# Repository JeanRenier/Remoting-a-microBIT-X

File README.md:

**Introduction.**
 I became a licensed radio amateur when I retired some 10 years ago, my call is ON4JRT.
 Alas, moving to an apartment building a few years ago I lost the possibility to install a decent antenna. Even if I had the permission to install an antenna on the roof, the QRM generated by the building itself and the surrounding town would probably have made a clean reception almost impossible.
 A friend, who lives in the country side and to whom I am eternally grateful, came to my rescue and allowed me to install a remote transceiver and a modest antenna in his garden.

There are several remote transceiver projects described on the internet. Whilst they all are certainly more sophisticated and more performing than the rather simple system presented here, they are also much more demanding in resources (space, power, money, ...). I wanted a small stand alone system that would be self sustaining (save for an internet connection), not too conspicuous and not too expensive.
 Hence this project, which eventually was successful after a few trials. Its aim is to provide me with an remotely located transceiver for my own use, it is by no means a &quot;public&quot; transceiver available to other OM&#39;s.
 Like all engineering endeavor it consist of a series of choices and compromises, so don&#39;t shoot the pianist.

**The concept.**
 The remote transceiver system consists of several parts: A transceiver (obviously), a HF antenna, a battery, a small solar panel, a controller with a WiFi transceiver and a controller for the solar panel. Except for the HF antenna and the solar panel everything is enclosed in a small plastic housing of about 5 liter in volume.
 The remote transceiver communicates (i.e. the bidirectional data flows for sound, CAT and control) over the internet with a home device. This home device contains a simple user interface allowing some control over the remote device. Sound input and output is also available on this home device, as is a CAT interface. If I were a better PC/Posix software programmer I would probably gotten rid of the home device. Having the home device as a physical thing eases however the development (at least for me) while not adding too much to the cost.

**The transceiver.**
 After some search, I came across the µBIT-X (&quot;[https://www.hfsignals.com/index.php/ubitx/](https://www.hfsignals.com/index.php/ubitx/)&quot;) sold as a semi assembled kit developed by Ashhar Farhan (VU2ESE), now in its 6th version (I got the previous version for this project). It is a simple but rather well designed multi band HF QRP transceiver based on a double super architecture and bidirectional amplifiers (it uses almost all the building blocks for reception as well as for transmission). It is well documented, has a large fan club and most of the suggested improvements are officially endorsed.
 Coming out of the box, it needs to be calibrated and tuned (a bit). Apart from the CAT baud rate I didn&#39;t feel the need to modify anything. Obviously I didn&#39;t install the LCD or the rotary encoder (since nobody would look/touch at it), all control is performed via the CAT connection over the internet from the home device, and even then, very little of the CAT commands are really used.

**The µBIT-X controller, hardware.**

Beginning with the power supply: a DC/DC controller reduces the battery voltage to 4V, from there three linear regulators make the necessary 3.3V digital, 3.3V analog and 1.8V respectively.

An ESP32-WROOM module is the core of the controller, this awesome microprocessor includes the WiFi transceiver, performs all relevant IP chores and runs all the application software.
 It then interfaces a WM8731 codec by a I2Sbus for the digital sound and a I2Cbus for its control. This codec is a straight forward 16bit stereo ADC and DAC combination, it is programmed in this case for a sampling rate of 8kHz, yielding a sound bandwidth of 3400Hz, its dynamic range exceeds 90dB. The analog sound input and output from the codec goes through a set of isolating 600 Ohm 1:1 audio transformers and trimpots to the µBIT-X sound stages.
 The first UART of the ESP32 is exclusively used for programming and debugging.

The second UART interfaces the CAT of the µBIT-X including a PTT line. This interface is isolated with a set of optocouplers, limiting the baud rate to 4800. Note that the RD and TD lines of this interface actually bypass the USB-UART chip on the Arduino Nano board of the µBIT-X, luckily a series resistor was placed in the RD line of this Arduino Nano, hence no track cutting was nescessary.
 The third UART interfaces the Solar Controller board, it is also fit with optocouplers.
 At last the board is equipped with a PMOS switch capable of more than 2A to power the µBIT-X itself when required.

An additional small board comprising a simple tandem match type VSWR bridge is mounted directly on the antenna input/output of the µBIT-X. The detected forward and reflected signals are fed into the ADC inputs of the ESP32. With the help of some math and calibration, it gives a rather good indication of the HF power and VSWR during transmit.

**The µBIT-X controller, software.**

The software was build on the Arduino IDE (version 1.8.12) with the ESP32 plug in and libraries (version 1.0.4). It took several months of writing and careful testing, having the home device nearby was a great help.
 The software was not especially designed to be universal or portable. The several parameters like the IP addresses, URL&#39;s, etc. are &quot;hard coded&quot; in the software, no attempt was made for now to store them in a file structure or other form of non volatile memory. Hence there is no way to change them without recompiling the entire software.
 The software includes the interesting possibility of being updated &quot;over the air&quot;, i.e. via the WiFi as per the method recommended by Espressif. This was tested but not yet used, an additional port forwarding on the remote router is needed tor this.

The setup part of the software starts with the initialization of the several internal and external peripherals. After that a WiFi connection with one of the friendly WiFi AP&#39;s is established, that done the µBIT-X Controller will synchronizes with an NTP server, checking in at a DDNS server and send a short e-mail as a sign of live. Once the setup is done two endless loops will take care of business until powered off.
 One of the loops is dedicated to the audio interface, seeing to it that the digital sound samples flow in and out the codec through the I2Sbus at a constant rate of 8kHz.
 The other loop will handle the incoming and outgoing UDP packets. Outgoing packets are sent only when incoming UDP packets are present, i.e. only during a connection between the µBIT-X controller and the home device.

The data in each packet is split into three separate flows, the biggest one being the sound, a smaller one for the CAT going directly to/from the µBIT-X and the last one for the housekeeping of the µBIT-X Controller itself and the Solar Controller.

During a connection there is a UDP flow of 25 packets per second in each direction. Each packet has 660 bytes is build as follows:
 - bytes 0...639 : 320 16bit sound samples, 8000 samples/s

- byte 640...641 : packet count and control byte, including the PTT bit

- byte 642...646 : CAT bytes, max 5 to/from the µBIT-X

- byte 647...659 : CTL bytes, max 13 to/from the Solar Controller
 The sound samples of the incoming packets are stored in a circular buffer of 1s. Currently there is no provision made to cope with lost packets, if the circular buffer runs out, silence is send to the codec until its filled again for at least a quarter. Packet loss has not been a problem so far, typically no more than one packet per thousand gets lost.
 Likewise, differential drift of the sample clock, the 8kHz sampling rates at send and receive sides are not exactly equal, is simply ignored, though I may change this in future.

A few words about the IP addressing. In normal circumstances both the home device and µBIT-X Controller are connected to their respective WiFI AP&#39;s that are typically part of a modem router devices provided by Internet Access operators. The IP addresses of these devices are variable over time as the operators see fit. Hence the use of a DDNS server, the free service &quot;www.duckdns.org&quot; was chosen here. Both sides of the link are then known by their URL&#39;s i.e. &quot;remote\_name.duckdns.org&quot; and &quot;home\_name.duckdns.org&quot; respectively.
 That is one problem solved, still the packets need to pass the modem routers and be directed to the devices. This is done by setting a port forwarding for the appropriate port number in the modem router at both sides.
 Most modem routers have the tendency to assign a new IP address to the devices each time they connect. In order to avoid that, fixed IP addresses are organized for each device, hence the port forwarding can be set once and for all. The fixed IP addresses should carefully be chosen in order not to disturb the other IP stations on the local area (i.e. choosing one outside of the DHCP range of the modem).
 A more elegant solution to avoid the fixed IP addresses and the port forwarding settings in the modem routers would be the use of the UPnP method. There are good libraries for this method, e.g. &quot;[https://github.com/ofekp/TinyUPnP](https://github.com/ofekp/TinyUPnP)&quot;, with which I played a bit. It probably works but I was not able to test it due to some issues with my own modem router, so I stick with the port forwarding and fixed IP addresses for now.

**The solar panel controller.**
 The µBIT-X controller board (see further) takes about 38mA during normal operation (the µBIT-X itself being turned off), this was deemed too much to have it continuously running. Hence a scheme was preferred where the remote transceiver would become available through the internet for a few hours everyday at some predetermined time, e.g. from 8 o&#39;clock in the evening till midnight. This scheme works for me, though it may not be the case for everybody.

For this alarm clock/timer function a 24 hour real time clock was implemented in software. The power on time, the power off time and also the current time are settable remotely once a connection with the home device has been made.
 Besides of the above function the solar controller board is also supervising the charge of the battery. This function is kept extremely simple: when the battery voltage rises higher than 12.3V a PMOS switch is opened prohibiting the further charging of the battery from the solar panel. Likewise, if the battery voltage falls below 9.3V an other PMOS switch will cut the load (i.e. the rest of the system) in order to protect the battery from deep discharge damage. As the solar panel itself behaves very much like a current source and yields at most about 0.6A, no attempt is made to limit the charging current, it remains well below the maximum charging current of the Li-Ion battery.

This little board was designed some four years ago, it is built around the ATtiny84 chip and is furthermore connected via a serial port to the µBIT-X controller for housekeeping, such as the above mentioned timings, the battery voltage and the temperature inside the box. It takes a mere 3mA (continuously) from the battery.

**The battery.**
 Nothing very much is to be said about the battery, it is just an assembly of 18 Li-Ion cells of the 18650 format, 6 in parallel and 3 in series, yielding a nominal voltage of 11.1V and a capacity of 13Ah.
 Nothing is foreseen to perform load balancing, as is typical for Li-Ion batteries. After three &quot;campaigns&quot; in the field of 6 months each, no significant voltage drift was noted on the individual cell groups. This may be due to the rather gentle use of this battery, it is used mostly when nearly full (close to 12V), charged with no more than 0.6A (limited by the solar panel) and discharged with no more than 1.5A (µBIT-X transmitting) and the latter only during short periods.
 There is some concern about the temperature range of the the Li-Ion batteries: 0...40°C, which can easily be overreached during cold winters and hot summers. A thin Aluminum sheet is foreseen behind the south side of the housing to provide some shade for it.

**The housing.**
 A regular fridge/kitchen type PE box with a watertight lid of roughly 300\*200\*100mm (ca. 5 liter) was chosen as a housing for the entire remote system. An unorthodox choice, but there were never any problems with rain or weather during the accumulated 18 plus months of outdoor live so far.
 The box is traversed by two cables, one for the HF antenna (RG 58 coax) and one for the solar panel (round flexible twin electricity cable), both foreseen with pressure glands.
 Two &quot;feet&quot; are furthermore foreseen to enable the box to stand upright with its 200mm side vertical.
 The rear part of the box is reserved for the battery, the front part for the WiFi antenna (a double biquad), the in between space is filled with the µBIT-X, the µBIT-X controller and the solar controller. It was a bit of a shoe horn exercise, but nobody did complain...
 A few pouches of silica gel drying agent were inserted before the final closure of the lid.

**The solar panel.**
 The solar panel looks a bit like a picture frame, a slim Aluminum frame holds two sheets of glass between which 35 poly-crystalline photo voltaic cells are mounted in series. Its dimension is 330\*290mm. It is rated 10W by the manufacturer, if exposed perpendicular to the sun during a clear day it would yield about 17.5V (open circuit) and 0.6A (short circuit). It is installed in the garden more or less in an open space, near to the remote transceiver box, facing south and tilted at 45°.
 Theoretically, considering the statistics for my part of the world, it would yield 3.5Ah on an average summer day and 0.7Ah on an average winter day. Plenty to play with, at least during summer.

**The antenna.**
 Discretion is the keyword here, a simple 20m band wire dipole was installed horizontally between the trees in the garden. For practical reasons the resonant feed line design was chosen here, the height above the ground is about 3.5m. Alas, too low to make it a good DX antenna, but then it was that or nothing. The antenna is entirily made of RG58 cable, a nylon rope runs along with it for improved strength.
 The antenna impedance was measured and a small fixed LC circuit was installed in the remote transceiver box as an antenna tuner of sorts to ensure that the VSWR remains below 1.5.
 It was noted that the VSWR varies from 1.2 to 1.5 depending the weather.

**The home device, hardware.**
 The hardware of the little home device is very similar as that of the µBIT-X Controller. The sound is connected to the audio input/output of a PC with a 3.5mm audio jack. The incoming sound is also diverted to a small (30mm) loudspeaker to monitor the received signal.
 Note that the sound levels are kept intentionally high (i.e. around 1Veff), this in order to maximize the S/N ratio. The sound input/output towards the PC must hence be set accordingly (maximum for the output and almost nil for the input).
 The second UART is led through a UART-USB chip and is used for the CAT. The USB connection is also used for powering the home device. Further peripherals are a small OLED display (128\*64 pixels) connected to the I2Cbus (to monitor some vital parameters of the remote), a rotary encoder (to change the frequency), a potentiometer (speaker volume) and a toggle switch (to start/stop the connection with the remote).

**The home device, software.**
 The software of the little home device is also very similar to that of the µBIT-X Controller. No NTP synchronization or e-mail sending, instead the OLED display is configured during setup.
 During looping, the sending of packets is controlled by the toggle switch. Control and CAT messages coming from the remote are parsed and put on the OLED display: current frequency and mode, HF power out, VSWR, received packet count (at both ends), RSSI of the WiFi link (at both ends), battery voltage and temperature inside the housing.

A few words about the handling of the CAT messages. By design the µBIT-X emulates (at least the meaningful part of) the CAT messages of the Yeasu FT817/FT857 transceiver. This works well when the µBIT-X is connected directly to a PC, I could however not make it work when connected to through the chain of devices and the internet, most probably a question of delay.
 The following scheme was then implemented: The home device emulates in itself the above transceivers, responding immediately to satisfy the application on the PC. If something is changed (in practice the frequency or the mode) the corresponding message is send over the internet to the remote µBIT-X controller and to the µBIT-X itself. Any response of the latter is returned over the internet to the user interface of the home device.
 This scheme works well with Fldigi, however not at all with WSJT-X for reasons I have yet to understand. As for the PTT, three methods are simply used in parallel: the DTR method, the CAT method and the VOX method (implemented in software).

**Construction notes.**
The PCB&#39;s were designed with KiCad (version 5.1.6) in the form of a two layer board with generous ground planes. Most of the components are SMD though still solderable by hand.
 The board assembled in one panel were manufactured by jlcpcb.com, they offer an excellent and fast service. Care was taken to get all the boards within an area of 100\*100mm, their more or less permanent prototype discount offer.
 Most of the components were purchased at &quot;www.tme.eu&quot; and &quot;[www.r](http://www.reichelt.com/)[eichelt.com](http://www.reichelt.com/)&quot;. The more exotic components (OLED display, audio transformers, ESP32-WROOM module, WM8731A, …) were purchased at &quot;[www.aliexpress.com](http://www.aliexpress.com/)&quot;, the stuff is on the road for about 6 weeks, but the price is unbeatable.

In order to load the software into the ESP32 with the Arduino IDE, a small UART-USB module should be connected to the first UART (debug, only the RD, TD and GND lines), the boot strap should be shorted and the reset button should be pressed.
 The Solar Controlled was designed several years earlier, its software was made with AVR Studio 4. Alas, there is no Arduino IDE support for the ATtiny84.
 Finally, the housing of the home device was 3D-printed (a little box of 100\*50\*30mm), it was designed with OpenScad.

**Performance of the system as a whole.**

I am active only on the 20m band for now, the antenna being strictly monoband, and then mostly in the popular FT8 mode. With the 6...7W of output power it seems that I suffer some 10...15dB disadvantage versus other stations (difference of their S/N report versus my S/N report). This is probably more an issue of the QRP nature of the µBIT-X than the fact it is connected via the internet.
 The additional time delay due to digitization and buffering of the sound does not seem to have a significant effect, it is about 0.7s.

An other concern is the lack of cooling in the rather hermetic non metallic housing. When busy for one hour atempting QSO&#39;s in FT8, the temperature inside the housing will rise by typically 5°C. Not too bad, but then it says little about the temperature of the power FET&#39;s of the PA. Initial tests however indicated that their rather small radiators didn&#39;t became too hot even after several minutes of transmitting.

Battery drain of the remote part:
 - Solar Controller: 3mA (continuous)
 - µBIT-X Controller: 38mA (when awake)

- µBIT-X receiving: 175mA (when connected with the home device)
 - µBIT-X transmitting: 1125mA (when transmitting a single tone at 6W)

**Further improvements and other considerations.**
 Since the µBiT-X is multi band, as a further evolution of this project, I intend to have a multi band antenna (at least adding the 40m band) and some form of switchable/variable antenna tuner.

Some trick to capture the speed of rotation of the rotary encoder on the home device and to vary the frequency step accordingly would be useful. Now each step is strictly 100Hz, which is rather inconvenient. Making WSJT-X&#39;s CAT work with the home device would also be nice.
 Currently there is no provision made as for internet security, i.o.w. anybody with the right format of UDP packets can access the remote device and use it (he/she has still to know the relevant URL of course). Some scheme with an encrypted signature (e.g. HMAC style) inside each packet authenticating the home device would be an improvement.
 Though the current design is intended for the use with digimodes, it can easily be adapted for voice operations. Adding a microphone amplifier and a PTT switch input would then be required.

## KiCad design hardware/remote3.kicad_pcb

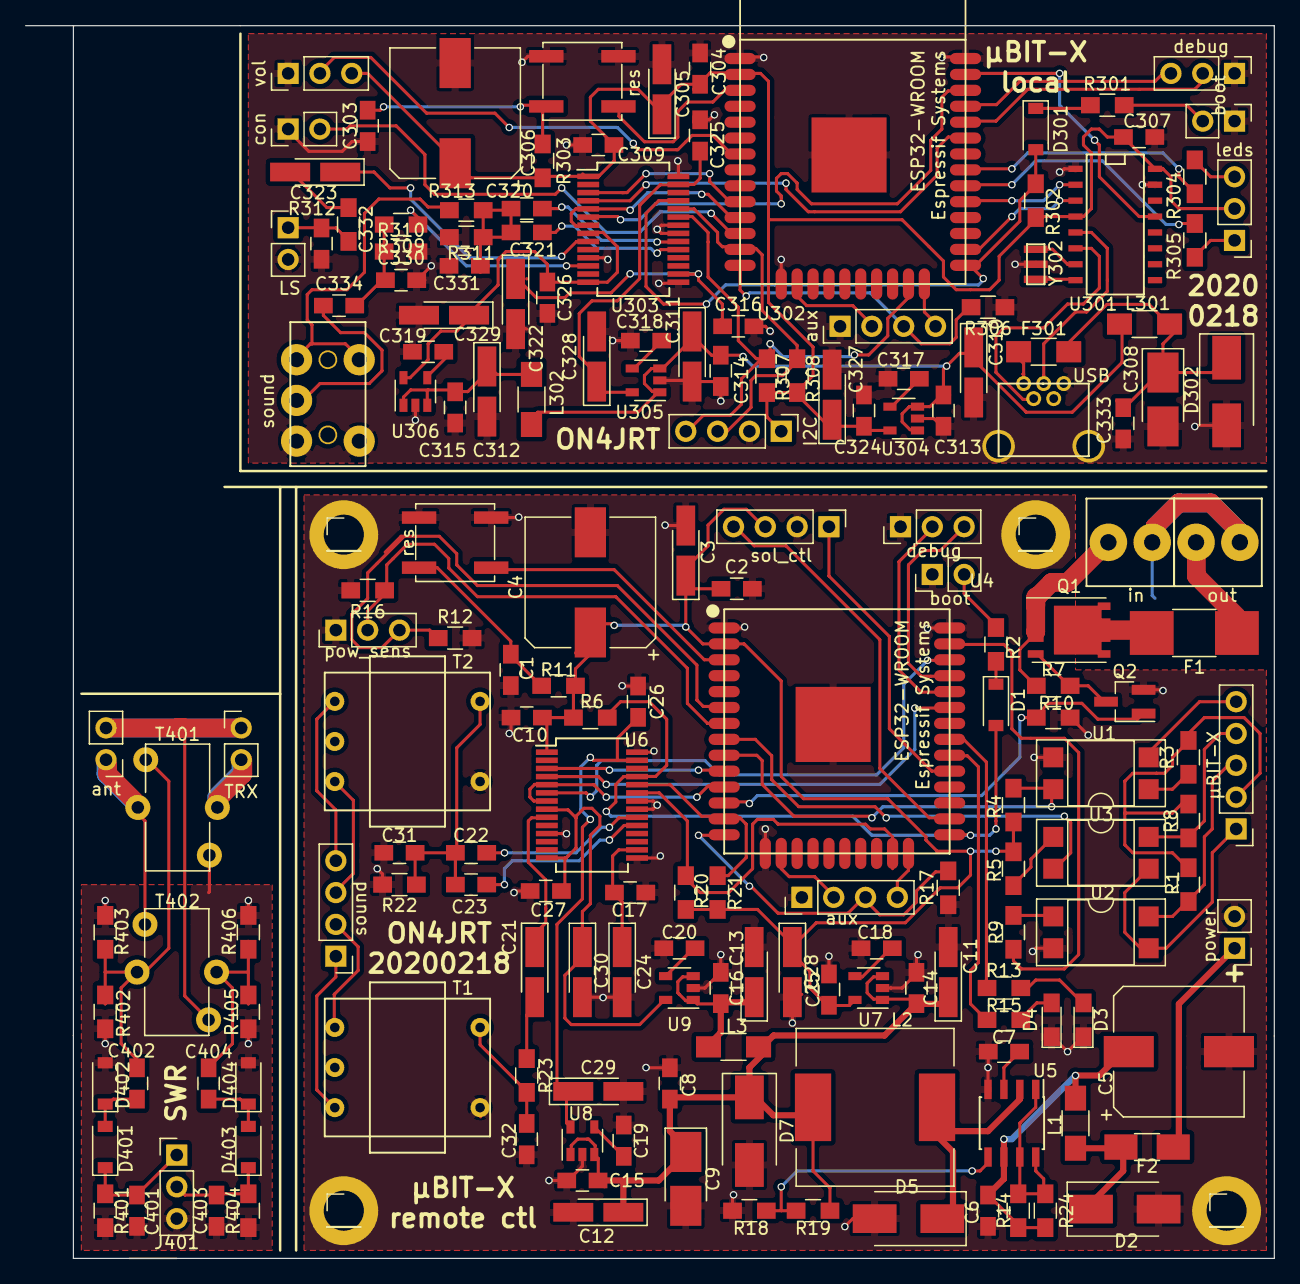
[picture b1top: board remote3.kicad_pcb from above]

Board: 2 copper layers, 99.7 x 98.4 mm, 182 parts (0 on the bottom side), 123 nets.

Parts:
 : hole; Pin_Header_Straight_1x01_Pitch2.54mm
 #2,  #3,  #4: hole; Pin_Header_Straight_1x01_Pitch2.54mm
C1, C303: 10n; C_0805_HandSoldering
C2, C6, C8, C10, C14, C15, C16, C17, C22, C23, C25, C26, C27, C304, C307, C309, C313, C314, C315, C316, C320, C321, C324, C325, C326, C333, C334, C401, C402, C403, C404: 100n; C_0805_HandSoldering
C3, C305: 1.5u; CP_Tantalum_Case-A_EIA-3216-18_Hand
C4, C306: 1500u; CP_Elec_10x10
C5: 470u; CP_Elec_10x10
C7, C18, C19, C20, C31, C32, C317, C318, C319, C330, C331, C332: 470p; C_0805_HandSoldering
C9, C308: 100u; CP_Tantalum_Case-B_EIA-3528-21_Hand
C11, C12, C13, C21, C24, C28, C29, C30, C310, C311, C312, C322, C327, C328, C329: 10u; CP_Tantalum_Case-A_EIA-3216-18_Hand
C323: 100u; CP_Tantalum_Case-A_EIA-3216-18_Hand
D1, D301: 1N4148; D_SOD-123
D2: 15V transil; D_SMB_Handsoldering
D3: green; LED_0805_HandSoldering
D4: red; LED_0805_HandSoldering
D5: D_Schottky; D_SMB_Handsoldering
D7, D302: 5.1V transil; D_SMB_Handsoldering
D401, D402, D403, D404: BAT85; D_SOD-123
F1: 2.6A; R_1812_HandSoldering
F2: 0.35A; Fuse_SMD1206_HandSoldering
F301: 0.35A; R_1206_HandSoldering
I2C: I2C; Pin_Header_Straight_1x04_Pitch2.54mm
J401: SWR; Pin_Header_Straight_1x03_Pitch2.54mm
L1, L3, L301, L302: 10u; L_1206_HandSoldering
L2: 100u; L_12x12mm_h8mm
LS: LS-32Ohm; Pin_Header_Straight_1x02_Pitch2.54mm
Q1: AO4407A; PowerPAK_SO-8_Single
Q2: BSS138; SOT-23_Handsoldering
R1, R8, R20, R21, R307, R308, R309, R313: 4.7k; R_0805_HandSoldering
R2, R5, R9, R13, R15, R301, R304, R305: 330; R_0805_HandSoldering
R3: 680; R_0805_HandSoldering
R4: 3.3k; R_0805_HandSoldering
R6, R7, R10, R11, R17, R18, R302, R303, R306, R401, R404: 10k; R_0805_HandSoldering
R12, R16: 100k; R_0805_HandSoldering
R14, R24: 1; R_0805_HandSoldering
R19: 22k; R_0805_HandSoldering
R22, R310, R311: 51k; R_0805_HandSoldering
R23: 33; R_0805_HandSoldering
R312: 10; R_0805_HandSoldering
R402, R403, R405, R406: 100; R_0805_HandSoldering
T1, T2: 600Ohm 1/1; Transformer_NF_ETAL_1-1_P1200
T401, T402: FT-37-43; L_Toroid_Vertical_L10.0mm_W5.0mm_P5.08mm
TRX: in; Pin_Header_Straight_1x02_Pitch2.54mm
U1, U2, U3: LTV-817; DIP-4_W7.62mm_SMDSocket_SmallPads
U4, U302: ESP32-WROOM
U5: MC34063; SOIC-8_3.9x4.9mm_Pitch1.27mm
U6, U303: WM8731; SSOP-28_5.3x10.2mm_Pitch0.65mm
U7, U9, U304, U306: tc1185-3.3V; SOT-23-5
U8, U305: tc1185-1.8V; SOT-23-5
U301: CH340G; SO-16-N
USB: USB_B mini; USB_Micro-B_Wuerth-614105150721_Vertical_CircularHoles
Y302: 12MHz; Resonator_SMD-3pin_7.2x3.0mm
ant: out; Pin_Header_Straight_1x02_Pitch2.54mm
aux: aux; Pin_Header_Straight_1x04_Pitch2.54mm
aux#2: aux; Pin_Header_Straight_1x04_Pitch2.54mm
boot: boot; Pin_Header_Straight_1x02_Pitch2.54mm
boot#2: boot; Pin_Header_Straight_1x02_Pitch2.54mm
con: connect; Pin_Header_Straight_1x02_Pitch2.54mm
debug: debug; Pin_Header_Straight_1x03_Pitch2.54mm
debug#2: debug; Pin_Header_Straight_1x03_Pitch2.54mm
in: battery; TerminalBlock_bornier-2_P5.08mm
leds: bicolor led; Pin_Header_Straight_1x03_Pitch2.54mm
out: UBITX; TerminalBlock_bornier-2_P5.08mm
pow_sens: pw_sens; Pin_Header_Straight_1x03_Pitch2.54mm
power: power; Pin_Header_Straight_1x02_Pitch2.54mm
res: reset; SW_SPST_EVPBF
res#2: reset; SW_SPST_EVPBF
sol_ctl: solctl; Pin_Header_Straight_1x04_Pitch2.54mm
sound: sound; PJ320E_3.5mm_Jack
sound#2: sound; Pin_Header_Straight_1x04_Pitch2.54mm
vol: volume; Pin_Header_Straight_1x03_Pitch2.54mm
µBIT-X: CAT; Pin_Header_Straight_1x05_Pitch2.54mm

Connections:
+3V3: C2.1, C3.1, C4.1, C10.1, C25.1, C28.1, C304.1, C305.1, C306.1, C307.1, C309.1, C324.1, C327.1, I2C.1, R4.1, R5.1, R6.1, R11.2, R20.2, R21.2, R302.1, R303.2, R307.2, R308.2, U4.2, U6.1, U7.5, U301.4, U301.16, U302.2, U303.1, U304.5, leds.2, sol_ctl.3, vol.3
GND: .1, #2.1, #3.1, #4.1, C1.2, C2.2, C3.2, C4.2, C5.2, C6.2, C7.2, C8.2, C9.2, C10.2, C11.2, C12.2, C13.2, C14.2, C15.2, C16.2, C17.2, C18.2, C19.2, C20.2, C24.2, C25.2, C26.2, C27.2, C28.2, C29.2, C30.2, C31.2, C32.2, C303.2, C304.2, C305.2, C306.2, C307.2, C308.2, C309.2, C310.2, C311.2, C312.2, C313.2, C314.2, C315.2, C316.2, C317.2, C318.2, C319.2, C322.2, C324.2, C325.2, C326.2, C327.2, C328.2, C329.2, C330.2, C331.2, C332.2, C333.2, C401.2, C403.2, D2.2, D3.1, D4.1, D5.2, D7.2, D302.2, D402.2, D404.2, I2C.2, J401.3, LS.2, Q2.1, R10.2, R12.2, R16.2, R17.1, R18.2, R22.2, R306.1, R310.2, R311.2, R401.2, R402.1, R403.1, R404.2, R405.1, R406.1, T1.2, T2.2, T401.3, U1.3, U2.2, U4.1, U4.15, U4.38, U4.39, U5.4, U6.11, U6.15, U6.21, U6.22, U6.28, U7.2, U8.2, U9.2, U301.1, U301.15, U302.1, U302.15, U302.38, U302.39, U303.11, U303.15, U303.21, U303.22, U303.28, U304.2, U305.2, U306.2, USB.5, USB.6, Y302.2, aux.1, aux#2.1, boot.1, boot#2.1, con.1, debug.1, debug#2.1, in.2, out.2, pow_sens.1, power.2, res.2, res#2.2, sol_ctl.2, sound.3, vol.1
unnamed: C1.1, R11.1, U4.3, res.1
unnamed: C5.1, C6.1, L1.2, R14.2, R24.2, U5.6
unnamed: C7.1, U5.3
unnamed: C8.1, C9.1, C11.1, C12.1, C14.1, C15.1, D7.1, L2.2, L3.1, R19.2, U7.1, U7.3, U8.1, U8.3
unnamed: C13.1, C16.1, L3.2, U9.1, U9.3
unnamed: C17.1, C24.1, U6.16
unnamed: C18.1, U7.4
unnamed: C19.1, U8.4
unnamed: C20.1, U9.4
unnamed: C21.1, U6.9
unnamed: C21.2, R23.2
unnamed: C22.1, C23.1, C31.1, R22.1, T2.1
unnamed: C22.2, U6.20
unnamed: C23.2, U6.19
unnamed: C26.1, C29.1, U6.27, U8.5
unnamed: C27.1, C30.1, U6.8, U6.14, U9.5
unnamed: C32.1, R23.1, T1.1
unnamed: C303.1, R303.1, U302.3, res#2.1
unnamed: C308.1, C333.1, D302.1, F301.2, L301.1
unnamed: C310.1, C311.1, C313.1, C314.1, L301.2, L302.1, U304.1, U304.3, U305.1, U305.3
unnamed: C312.1, C315.1, L302.2, U306.1, U306.3
unnamed: C316.1, C322.1, U303.16
unnamed: C317.1, U304.4
unnamed: C318.1, U305.4
unnamed: C319.1, U306.4
unnamed: C320.1, C321.1, C331.1, R311.1, R313.2
unnamed: C320.2, U303.20
unnamed: C321.2, U303.19
unnamed: C323.1, U303.9
unnamed: C323.2, R312.2
unnamed: C325.1, C328.1, U303.27, U305.5
unnamed: C326.1, C329.1, U303.8, U303.14, U306.5
unnamed: C330.1, C334.2, R309.2, R310.1
unnamed: C332.1, LS.1, R312.1
unnamed: C334.1, sound.2
unnamed: C401.1, D401.1, J401.1, R401.1
unnamed: C402.1, R402.2, R403.2, T401.4, T402.4
unnamed: C402.2, D401.2, D402.1
unnamed: C403.1, D403.1, J401.2, R404.1
unnamed: C404.1, R405.2, R406.2, T402.3
unnamed: C404.2, D403.2, D404.1
unnamed: D1.1, R2.1
unnamed: D1.2, R6.2, U4.25, U6.25
unnamed: D2.1, F2.2, L1.1
unnamed: D3.2, R13.2
unnamed: D4.2, R15.2
unnamed: D5.1, L2.1, U5.2
unnamed: D301.1, R301.1
unnamed: D301.2, R302.2, U302.25, U303.25
unnamed: F1.1, out.1
unnamed: F1.2, Q1.2
unnamed: F2.1, power.1
unnamed: F301.1, USB.1
unnamed: Q1.1, R7.1, in.1
unnamed: U4.29, sol_ctl.1
unnamed: U4.26, sol_ctl.4
unnamed: U4.34, debug.2
unnamed: U4.35, debug.3
unnamed: R2.2, boot.2
unnamed: U2.3, U3.3, µBIT-X.1
unnamed: R1.1, R3.2, R8.2, µBIT-X.2
unnamed: R1.2, U2.4, µBIT-X.3
unnamed: R8.1, U3.4, µBIT-X.4
unnamed: U1.2, µBIT-X.5
unnamed: R16.1, U4.7, pow_sens.2
unnamed: R12.1, U4.6, pow_sens.3
unnamed: U4.16, aux#2.2
unnamed: R17.2, U4.14, aux#2.3
unnamed: U4.24, aux#2.4
unnamed: T1.4, sound#2.1
unnamed: T1.3, sound#2.2
unnamed: T2.4, sound#2.3
unnamed: T2.3, sound#2.4
unnamed: R301.2, boot#2.2
unnamed: U302.34, debug#2.2
unnamed: U302.35, debug#2.3
unnamed: U302.7, vol.2
unnamed: U302.12, con.2
unnamed: U301.6, USB.2
unnamed: U301.5, USB.3
unnamed: R305.2, leds.1
unnamed: R304.2, leds.3
unnamed: I2C.3, R308.1, U302.13, U303.24
unnamed: I2C.4, R307.1, U302.23, U303.23
unnamed: U302.16, aux.2
unnamed: R306.2, U302.14, aux.3
unnamed: U302.24, aux.4
unnamed: R313.1, sound.1
unnamed: T401.1, T402.1, ant.1
unnamed: T402.2, TRX.1, ant.2
unnamed: T401.2, TRX.2
unnamed: Q1.3, Q2.2, R7.2
unnamed: Q2.3, R10.1, U4.12
unnamed: R3.1, U1.1
unnamed: R4.2, U1.4, U4.9
unnamed: R5.2, U3.1
unnamed: R9.1, U2.1
unnamed: R9.2, U4.37
unnamed: R13.1, U4.31
unnamed: R14.1, R24.1, U5.1, U5.7, U5.8
unnamed: R15.1, U4.30
unnamed: R18.1, R19.1, U5.5
unnamed: R20.1, U4.23, U6.23
unnamed: R21.1, U4.13, U6.24
unnamed: R304.1, U302.31
unnamed: R305.1, U302.30
unnamed: R309.1, U303.12
unnamed: U3.2, U4.8
unnamed: U4.10, U6.3
unnamed: U4.11, U6.5, U6.7
unnamed: U4.33, U6.4
unnamed: U4.36, U6.6
unnamed: U301.2, U302.29
unnamed: U301.3, U302.26
unnamed: U301.7, Y302.1
unnamed: U301.8, Y302.3
unnamed: U301.13, U302.37
unnamed: U302.10, U303.3
unnamed: U302.11, U303.5, U303.7
unnamed: U302.33, U303.4
unnamed: U302.36, U303.6

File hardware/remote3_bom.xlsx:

Id | Designator | Package | Quantity | Designation | Supplier and ref
Semiconductors
1 | U302 | ESP32-WROOM | 1 | ESP32-WROOM 32D with PCB antenna | AliExpress
2 | U4 | ESP32-WROOM | 1 | ESP32-WROOM 32U with IPEX connector | AliExpress
3 | U1,U2,U3 | DIP-4_W7.62mm_SMDSocket_SmallPads | 3 | SFH1690AT
4 | U5 | SOIC-8_3.9x4.9mm_Pitch1.27mm | 1 | MC34063
5 | U6,U303 | SSOP-28_5.3x10.2mm_Pitch0.65mm | 2 | WM8731 | AliExpress
6 | U7,U9,U304,U306 | SOT-23-5 | 4 | tc1185-3.3V
7 | U8,U305 | SOT-23-5 | 2 | tc1185-1.8V
8 | U301 | SO-16-N | 1 | CH340G | AliExpress
9 | Q1 | PowerPAK_SO-8_Single | 1 | AO4407A
10 | Q2 | SOT-23_Handsoldering | 1 | BSS138
11 | D3 | LED_0805_HandSoldering | 1 | green
12 | D4 | LED_0805_HandSoldering | 1 | red
13 | D1,D301 | D_SOD-123 | 2 | 1N4148
14 | D2 | D_SMB_Handsoldering | 1 | 15V transil
15 | D7,D302 | D_SMB_Handsoldering | 2 | 5.1V transil
16 | D5,D401,D402,D403,D404 | D_SOD-123 | 5 | BAT85
Inductors
17 | L1,L3,L301,L302 | L_1206_HandSoldering | 4 | 10u
18 | L2 | L_12x12mm_h8mm | 1 | 100u
19 | T401,T402 | L_Toroid_Vertical_L10.0mm_W5.0mm_P5.08mm | 2 | FT-37-43
Capacitors
20 | C7,C18,C19,C20,C31,C32,C317,C318,C319,C330,C331,C332 | C_0805_HandSoldering | 12 | 470p
21 | C1,C303 | C_0805_HandSoldering | 2 | 10n
22 | C2,C6,C8,C10,C14,C15,C16,C17,C22,C23,C25,C26,C27,C304,C307,C309,C313,C314,C315,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 | C_0805_HandSoldering | 31 | 100n
23 | C3,C305 | CP_Tantalum_Case-A_EIA-3216-18_Hand | 2 | 1.5u
24 | C11,C12,C13,C21,C24,C28,C29,C30,C310,C311,C312,C322,C327,C328,C329 | CP_Tantalum_Case-A_EIA-3216-18_Hand | 15 | 10u
25 | C9,C308,C323 | CP_Tantalum_Case-B_EIA-3528-21_Hand | 3 | 100u
26 | C5 | CP_Elec_10x10 | 1 | 470u, 16V
27 | C4,C306 | CP_Elec_10x10 | 2 | 1500u, 6V
Resistors
28 | R14,R24 | R_0805_HandSoldering | 2 | 1
29 | R312 | R_0805_HandSoldering | 1 | 10
30 | R23 | R_0805_HandSoldering | 1 | 33
31 | R402,R403,R405,R406 | R_0805_HandSoldering | 4 | 100
32 | R2,R5,R9,R13,R15,R301,R304,R305 | R_0805_HandSoldering | 8 | 330
33 | R3 | R_0805_HandSoldering | 1 | 680
34 | R4 | R_0805_HandSoldering | 1 | 3.3k
35 | R1,R8,R20,R21,R307,R308,R309,R313 | R_0805_HandSoldering | 8 | 4.7k
36 | R6,R7,R10,R11,R17,R18,R302,R303,R306,R401,R404 | R_0805_HandSoldering | 11 | 10k
37 | R19 | R_0805_HandSoldering | 1 | 22k
38 | R12,R16 | R_0805_HandSoldering | 2 | 100k
39 | R22,R310,R311 | R_0805_HandSoldering | 3 | 51k
Other
40 | Y302 | Resonator_SMD-3pin_7.2x3.0mm | 1 | 12MHz | AliExpress
41 | T2,T1 | Transformer 13.5*13.4*9.1mm | 2 | 1:1, 600Ohm, 1.6H, | AliExpress
42 | push button | SW_SPST_EVPBF | 2 | reset
43 | F2,F301 | R_1206_HandSoldering | 2 | 0.35A
44 | F1 | R_1812_HandSoldering | 1 | 2.6A
Connectors
45 | USB_B_mini | USB mini_B THT, angled | 1 | JST: UB-M5BR-DM14-4D
46 | sound | PJ320E_3.5mm_Jack | 1 | salvage
47 | in,out | TerminalBlock_bornier-2_P5.08mm | 2
48 | in | TerminalBlock_bornier-2_P5.08mm | 1
49 | diverse | Pin_Header_Straight_1x10_Pitch2.54mm | 5 | breakable
Off board
50 | potentiometer | 6mm shaft, hole mount, 10k linear | 1 | plus dito knob
51 | rotary encoder | 6mm shaft, incl. push switch | 1 | plus dito knob | AliExpress
52 | loadspeaker | Miniature: 30mm diam., 32 Ohm | 1 |  | AliExpress
53 | OLED display | 0,96” diagonal, 128*64 pixels, white/blue, IC2 interface | 1 |  | AliExpress
54 | toggle switch | 6mm shaft, hole mount, SPST | 1
55 | leds | 5mm led, common anode | 1 | bicolor led (red/green)
56 | diverse | Pin_Header_Female Straight_1x10_Pitch2.54mm | 5

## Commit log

2020-07-14 adding files
